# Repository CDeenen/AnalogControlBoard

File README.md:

# AnalogControlBoard
The analog control board (ACB) is a complete solution for all your analog and digital input and output needs. The board has 8 16-bit analog output ports, 16 16-bit analog input ports and 32 digital GPIOs (general purpose inputs/outputs). The board is controlled with a NXP LPC1768 microcontroller that can be communicated with through the USB port.

More info can be found in the wiki: https://github.com/CDeenen/AnalogControlBoard/wiki

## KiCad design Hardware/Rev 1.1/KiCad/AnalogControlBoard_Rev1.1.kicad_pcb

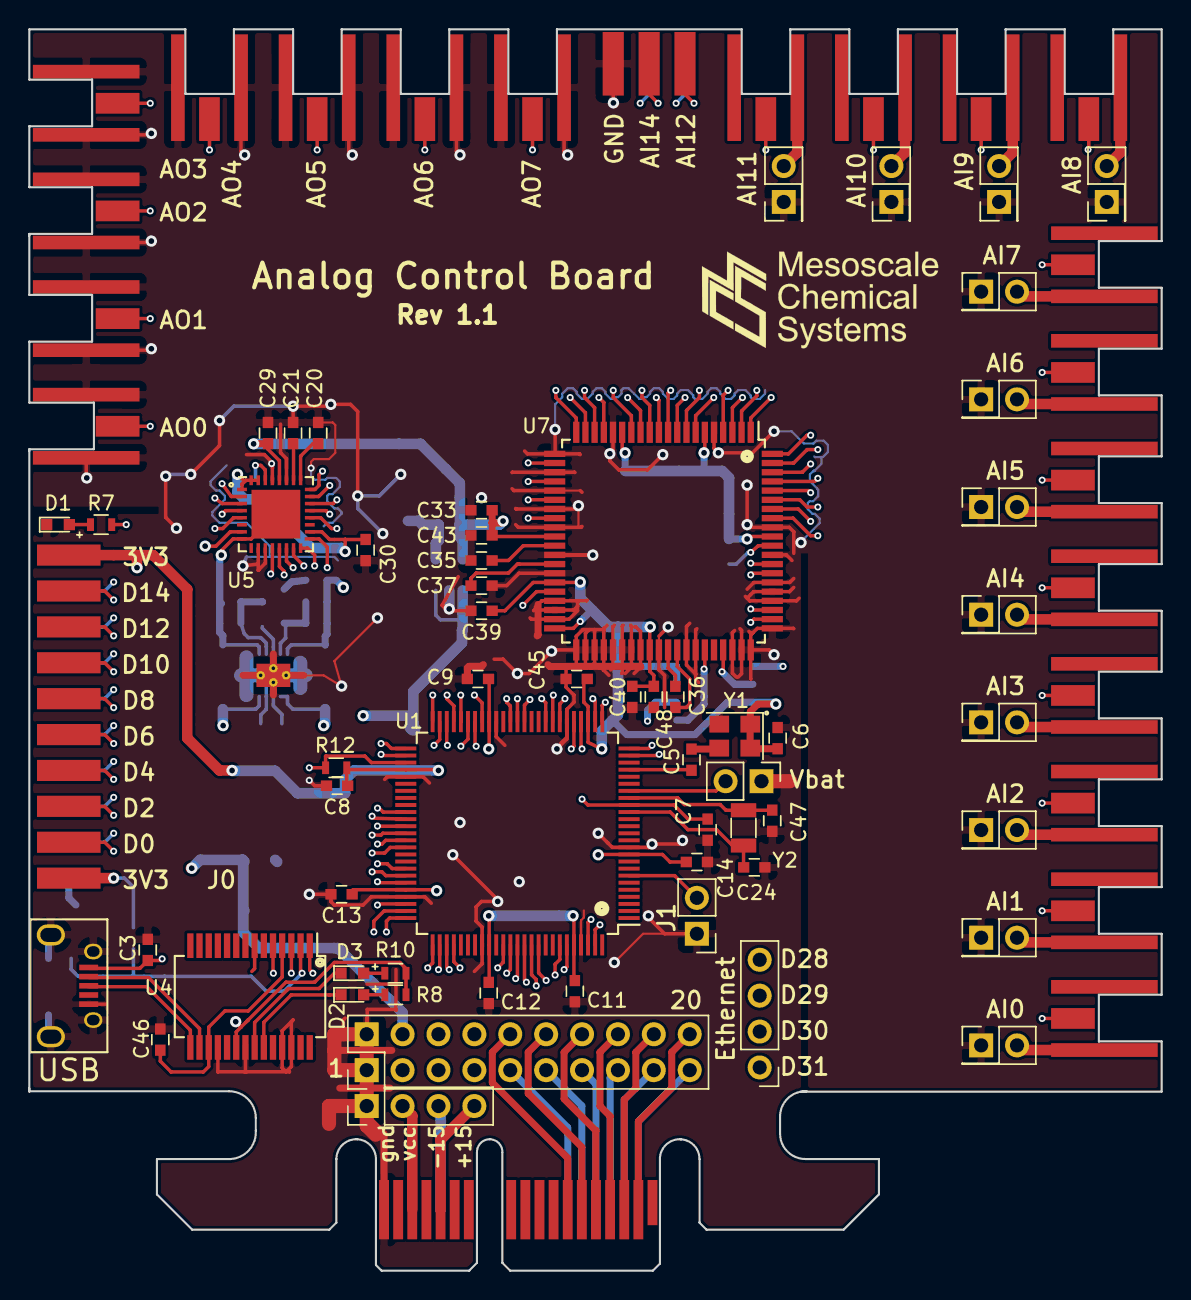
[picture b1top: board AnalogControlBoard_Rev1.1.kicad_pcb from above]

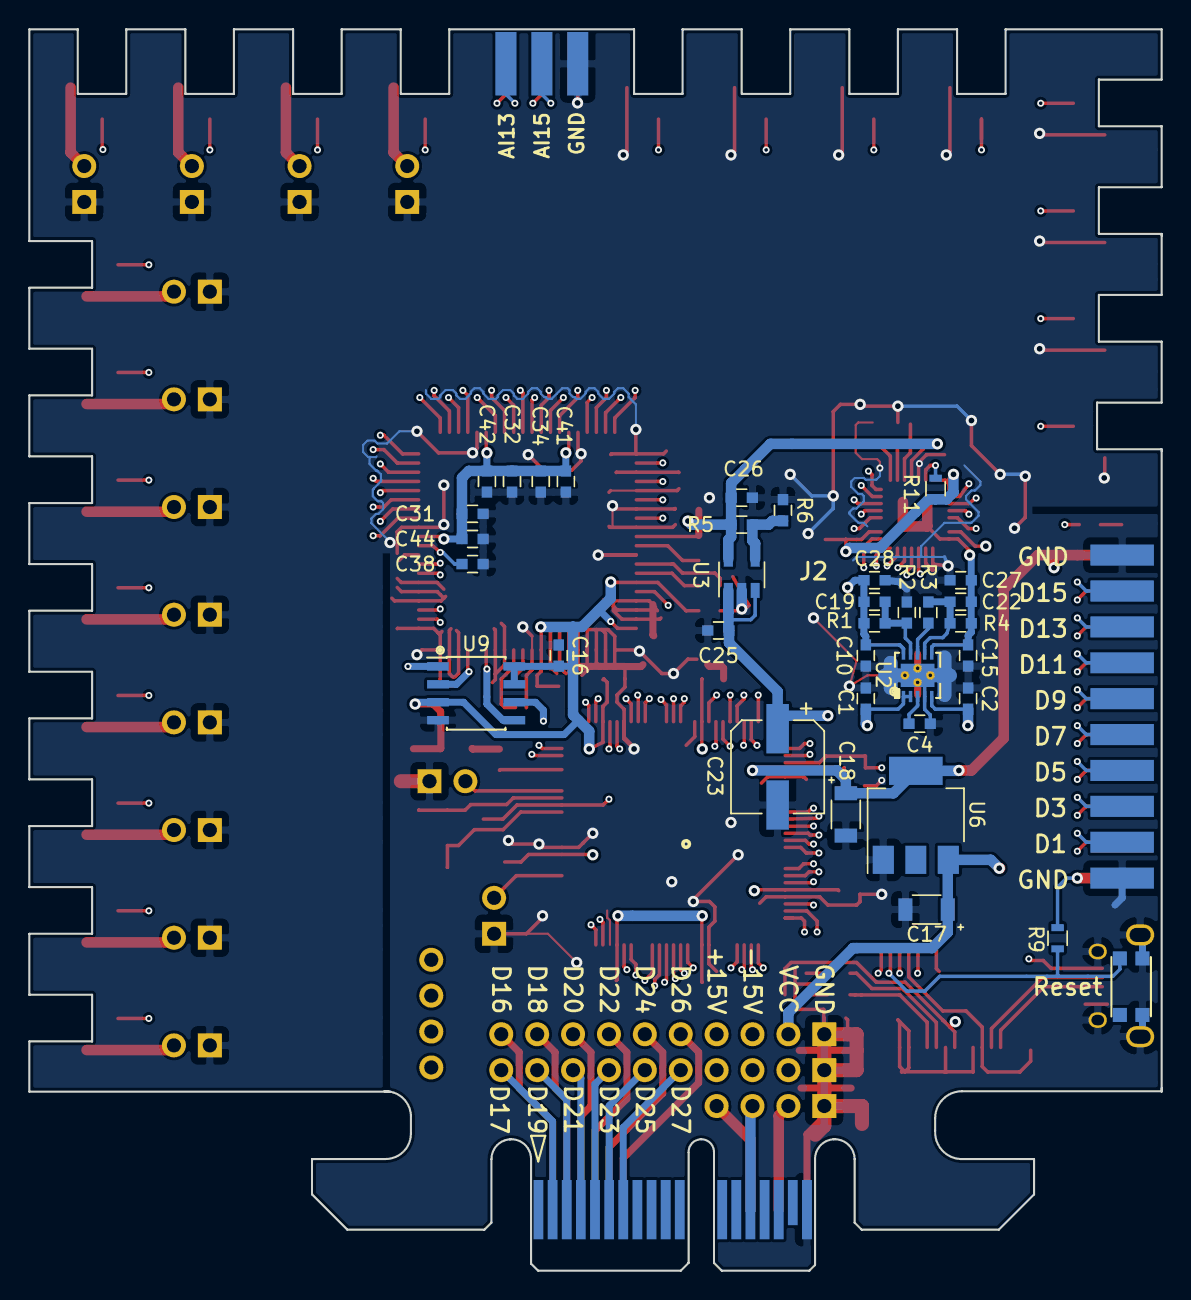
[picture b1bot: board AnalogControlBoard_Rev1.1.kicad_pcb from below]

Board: 4 copper layers, 80.1 x 87.9 mm, 115 parts (36 on the bottom side), 123 nets.

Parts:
C1, C2, C10, C15, C31, C32, C33, C34, C36, C38, C40: 10uF; C_0603
C3, C27, C28, C29, C39: 1uF; C_0603
C4, C19, C22: 10nF; C_0603
C5: 100pF; C_0603
C6, C7, C20, C21, C25, C26, C30, C41, C42, C43, C44, C46: 100nF; C_0603
C8, C9, C11, C12, C13, C14, C16, C45: 0.1uF; C_0603
C17: 10uF Tantalum; C_1206
C18: 22uF Tantalum; C_1206
C23: 100uF; CP_Elec_6.3x7.7
C24, C47: 18pF; C_0603
C35: 10uF Low ESR, X5R; C_0603
C37: 100nF, X8R; C_0603
C48: 100nF; Capacitor_0603
D1, D2, D3: LED; LED_0603
J1: EEPROM_CLEAR; Pin_Header_Straight_1x02_Pitch2.54mm
J2: Conn_02x10_Odd_Even; 2x10pinSideMount
J3: USB_OTG; MicroUSB_B
J4: Conn_PCI36; PCI-36
J5: JAI0; Pin_Header_Straight_2x01_Pitch2.54mm
J6: JAI1; Pin_Header_Straight_2x01_Pitch2.54mm
J7: JAI2; Pin_Header_Straight_2x01_Pitch2.54mm
J8: JAI3; Pin_Header_Straight_2x01_Pitch2.54mm
J9: JAI4; Pin_Header_Straight_2x01_Pitch2.54mm
J10: JAI5; Pin_Header_Straight_2x01_Pitch2.54mm
J11: JAI6; Pin_Header_Straight_2x01_Pitch2.54mm
J12: JAI7; Pin_Header_Straight_2x01_Pitch2.54mm
J13: JAI8; Pin_Header_Straight_2x01_Pitch2.54mm
J14: JAI9; Pin_Header_Straight_2x01_Pitch2.54mm
J15: JAI10; Pin_Header_Straight_2x01_Pitch2.54mm
J16: JAI11; Pin_Header_Straight_2x01_Pitch2.54mm
J17: Conn_02x03_Odd_Even; 2x3pinSideMount
J18, J20: Conn_01x04; Pin_Header_Straight_1x04_Pitch2.54mm
J22: Conn_02x10_Odd_Even; Pin_Header_Straight_2x10_Pitch2.54mm
J23: Vbat; Pin_Header_Straight_1x02_Pitch2.54mm
P1: AI0; MMCXconnector
P3: AI1; MMCXconnector
P6: AI2; MMCXconnector
P7: AI3; MMCXconnector
P8: AI4; MMCXconnector
P9: AI5; MMCXconnector
P10: AI6; MMCXconnector
P11: AI7; MMCXconnector
P12: AI8; MMCXconnector
P13: AI9; MMCXconnector
P14: AI10; MMCXconnector
P15: AI11; MMCXconnector
P20: AO3; MMCXconnector
P21: AO2; MMCXconnector
P22: AO1; MMCXconnector
P23: AO0; MMCXconnector
P24: AO7; MMCXconnector
P25: AO6; MMCXconnector
P26: AO5; MMCXconnector
P27: AO4; MMCXconnector
R1: 90.9K; C_0603
R2, R3: 10K; C_0603
R4: 100K; C_0603
R5: 76.8K; C_0603
R6: 24.9K; C_0603
R7, R8, R10: 220R; R_0603
R9, R11, R12: 10K; R_0603
SW1: SW_DPST; Switch
U1: LPC1768; LQFP-100_14x14mm_Pitch0.5mm
U2: TPS7A39; WSON-10_3x3mm_Pitch0.5mm_ThermalVias
U3: TPS73201-EP; SOT-23-5
U4: FT232RL; SSOP-28_5.3x10.2mm_Pitch0.65mm
U5: LTC2666; QFN-32-1EP_5x5mm_Pitch0.5mm
U6: LM1117; SOT-223-3_TabPin2
U7: AD7616; LQFP-80_14x14mm_Pitch0.65mm
U9: AT25_EEPROM; SOIC-8_3.9x4.9mm_Pitch1.27mm
Y1: ASE_12_LCT; Crystal_SMD_3225-4pin_3.2x2.5mm
Y2: 32.768KHz RTC Crystal; Crystal_SMD_3215-2pin_3.2x1.5mm

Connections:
3v3: C6.2, C8.1, C9.1, C11.1, C12.1, C13.1, C14.1, C16.2, C18.1, C30.1, C39.1, C40.1, C45.1, C48.1, J2.1, J2.19, R9.2, R11.2, R12.1, U1.10, U1.28, U1.42, U1.54, U1.71, U1.84, U1.96, U5.1, U5.18, U5.31, U5.32, U6.2, U7.35, U7.40, U7.49, U9.3, U9.7, U9.8, Y1.1, Y1.4
5V: C26.2, C29.2, C31.2, C32.2, C33.2, C34.2, C41.2, C42.2, C43.2, C44.2, R5.2, U3.5, U5.28, U7.6, U7.15, U7.30, U7.71
+7Vanalog: J4.A17, J4.B17
+7Vdigital: C17.1, C23.1, C25.2, J4.A16, J4.B16, J20.2, J22.3, J22.4, U3.1, U3.3, U6.3
+12V: C10.1, C19.1, C28.2, R1.2, U2.10, U5.7
+15V: C1.1, J4.A14, J20.4, J22.7, J22.8, U2.1, U2.2
-12V: C15.2, C22.2, C27.2, R4.1, U2.6, U5.8
-15V: C2.2, J4.B14, J20.3, J22.5, J22.6, U2.5
AB12: J4.A12, J4.B12
AD_BUSY: U1.32, U7.67
AD_CONVST: U1.33, U7.68
AD_CS: U1.27, U7.63
AD_MISO: U1.37, U5.15, U7.57, U9.2
AD_MOSI: U1.38, U5.16, U7.55, U9.5
AD_RESET: U1.39, U7.36
AD_SCLK: U1.34, U5.14, U7.62, U9.6
AI0: P1.2, U7.73
AI0_GND: J5.2, P1.1, U7.74
AI1: P3.2, U7.75
AI1_GND: J6.2, P3.1, U7.76
AI2: P6.2, U7.77
AI2_GND: J7.2, P6.1, U7.78
AI3: P7.2, U7.79
AI3_GND: J8.2, P7.1, U7.80
AI4: P8.2, U7.2
AI4_GND: J9.2, P8.1, U7.1
AI5: P9.2, U7.4
AI5_GND: J10.2, P9.1, U7.3
AI6: P10.2, U7.7
AI6_GND: J11.2, P10.1, U7.8
AI7: P11.2, U7.9
AI7_GND: J12.2, P11.1, U7.10
AI8_GND: J13.2, P12.1, U7.11
AI9: P13.2, U7.14
AI9_GND: J14.2, P13.1, U7.13
AI10: P14.2, U7.17
AI10_GND: J15.2, P14.1, U7.18
AI11: P15.2, U7.19
AI11_GND: J16.2, P15.1, U7.20
AI12: J17.5, U7.22
AI13: J17.6, U7.24
AI14: J17.3, U7.26
AI15: J17.4, U7.28
EEPROM_CS: U1.26, U9.1
EnetRxD0: J18.2, U1.91
EnetRxD1: J18.1, U1.90
EnetTxD0: J18.4, U1.95
EnetTxD1: J18.3, U1.94
GND: C1.2, C2.1, C3.2, C4.1, C6.1, C7.2, C8.2, C9.2, C10.2, C11.2, C12.2, C13.2, C14.2, C15.1, C16.1, C17.2, C18.2, C20.1, C21.2, C23.2, C24.2, C25.1, C26.1, C27.1, C28.1, C29.1, C30.2, C31.1, C32.1, C33.1, C34.1, C35.1, C37.2, C38.1, C39.2, C40.2, C41.1, C42.1, C43.1, C44.1, C45.2, C46.1, C47.2, C48.2, D1.1, J1.1, J2.2, J2.20, J3.5, J3.6, J4.A18, J4.B18, J5.1, J6.1, J7.1, J8.1, J9.1, J10.1, J11.1, J12.1, J13.1, J14.1, J15.1, J16.1, J17.1, J17.2, J20.1, J22.1, J22.2, J23.1, P20.1, P21.1, P22.1, P23.1, P24.1, P25.1, P26.1, P27.1, R2.1, R6.2, SW1.2, U1.11, U1.31, U1.41, U1.55, U1.72, U1.83, U1.97, U2.4, U3.2, U4.21, U4.25, U4.26, U5.10, U5.11, U5.27, U5.29, U6.1, U7.5, U7.16, U7.21, U7.23, U7.25, U7.27, U7.29, U7.32, U7.34, U7.37, U7.38, U7.39, U7.41, U7.42, U7.43, U7.44, U7.45, U7.46, U7.47, U7.48, U7.50, U7.53, U7.54, U7.58, U7.59, U7.60, U7.61, U7.64, U7.65, U7.66, U7.69, U7.72, U9.4, Y1.2
GPIO_CS: J2.11, U1.63
GPIO_INT0: J2.16, U1.51
GPIO_INT1: J2.15, U1.52
GPIO_MISO: J2.13, U1.61
GPIO_MOSI: J2.14, U1.60
GPIO_PWM0: J2.8, U1.68
GPIO_PWM1: J2.7, U1.69
GPIO_PWM2: J2.6, U1.70
GPIO_PWM3: J2.5, U1.73
GPIO_RX: J2.10, U1.64
GPIO_SCK: J2.12, U1.62
GPIO_SCL: J2.18, U1.47
GPIO_SDA: J2.17, U1.46
GPIO_TX: J2.9, U1.65
GPIO_USB_D+: J2.3, U1.29
GPIO_USB_D-: J2.4, U1.30
ISP_SEL: R12.2, U1.53, U4.3
LTC_CLR: U1.48, U5.24
LTC_CS: U1.44, U5.13
LTC_LDAC: U1.45, U5.12
LTC_OVRTMP: R11.1, U1.49, U5.30
LTC_TGP: U1.43, U5.17
unnamed: C4.2, U2.3
unnamed: C5.1, U1.22
unnamed: C5.2, Y1.3
unnamed: C19.2, R1.1, R2.2, U2.9
unnamed: C20.2, U5.25
unnamed: C21.1, U5.26
unnamed: C22.1, R3.1, R4.2, U2.7
unnamed: C24.1, U1.16, Y2.1
unnamed: C35.2, U7.31
unnamed: C36.1, U7.51
unnamed: C36.2, U7.52
unnamed: C37.1, U7.33
unnamed: C38.2, U7.70
unnamed: C46.2, U4.4, U4.17
unnamed: C47.1, U1.18, Y2.2
unnamed: D1.2, R7.1
unnamed: D2.1, U4.23
unnamed: D2.2, R8.1
unnamed: D3.1, U4.22
unnamed: D3.2, R10.1
unnamed: J1.2, U1.7
unnamed: J3.2, U4.16
unnamed: J3.3, U4.15
unnamed: J23.2, U1.19
unnamed: P20.2, U5.2
unnamed: P21.2, U5.3
unnamed: P22.2, U5.4
unnamed: P23.2, U5.5
unnamed: P24.2, U5.20
unnamed: P25.2, U5.21
unnamed: P26.2, U5.22
unnamed: P27.2, U5.23
unnamed: R3.2, U2.8
unnamed: R5.1, R6.1, U3.4
unnamed: R7.2, U1.50
PCI_GPIO0: J4.B5, J22.13, U1.89
PCI_GPIO1: J4.A5, J22.14, U1.88
PCI_GPIO2: J4.B6, J22.11, U1.87
PCI_GPIO3: J4.A6, J22.12, U1.86
PCI_I2C_SCL: J4.A2, J22.20, U1.24
PCI_I2C_SDA: J4.B2, J22.19, U1.25
PCI_SPI_MISO: J4.A4, J22.16, U1.77
PCI_SPI_MOSI: J4.B4, J22.15, U1.76
PCI_SPI_SCK: J4.B3, J22.17, U1.78
PCI_SPI_SSEL: J4.A3, J22.18, U1.79
PCI_UART_RX: J4.B7, J22.9, U1.74
PCI_UART_TX: J4.A7, J22.10, U1.75
RESET: C7.1, R9.1, SW1.1, U1.17, U4.2
USB_RX: U1.99, U4.1
USB_TX: U1.98, U4.5
V1: J4.A13, J4.B13
Vbus: C3.1, J3.1, R8.2, R10.2, U4.20

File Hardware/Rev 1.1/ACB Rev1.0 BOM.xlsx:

Column2 | Reference(s) | Value | Footprint | Specific | Article Nr
11 | C1, C2, C10, C15, C31, C32, C33, C34, C36, C38, C40 | 10uF | SMD 0603
5 | C3, C27, C28, C29, C39 | 1uF | SMD 0603
3 | C4, C19, C22 | 10nF | SMD 0603
1 | C5 | 100pF | SMD 0603
21 | C6, C7, C8, C9, C11, C12, C13, C14, C16, C20, C21, C25, C26, C30, C41, C42, C43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 | 100nF | SMD 0603
1 | C17 | 10uF Tantalum | SMD 1206
1 | C18 | 22uF Tantalum | SMD 1206
1 | C23 | 100uF | SMD 6.3x7.7
2 | C24, C47 | 18pF | SMD 0603
1 | C35 | 10uF Low ESR, X5R | SMD 0603
1 | C37 | 100nF, X8R | SMD 0603
1 | R1 | 90.9K | SMD 0603
5 | R2, R3, R9, R11, R12 | 10K | SMD 0603
1 | R4 | 100K | SMD 0603
1 | R5 | 76.8K | SMD 0603
1 | R6 | 24.9K | SMD 0603
3 | R7, R8, R10 | 220R | SMD 0603
3 | D1, D2, D3 | LED | SMD 0603
14 | J1, J5, J6, J7, J8, J9, J10, J11, J12, J13, J14, J15, J16, J23 | 1x2 Pin Header | 1x2 Pin Header
2 | J2, J22 | 2x10 Pin Header | 2x10 Pin Header
1 | J17 | 2x3 Pin Header | 2x3 Pin Header
2 | J18, J20 | 1x4 Pin Header | 1x4 Pin Header
1 | J3 | USB_OTG | MicroUSB_B | HRS | ZX62D-B-5P8(30)
20 | P1, P3, P6, P7, P8, P9, P10, P11, P12, P13, P14, P15, P20, P21, P22, P23, P24, 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 | MMCX Connector | MMCXconnector - Edge Mount | Molex | 73415-0961
1 | SW1 | Switch | Switch | C&K | KMR231GLFS
1 | U1 | LPC1768 | LQFP-100_14x14mm_Pitch0.5mm | NPX | LPC1768FBD100
1 | U2 | TPS7A39 | WSON-10_3x3mm_Pitch0.5mm_ThermalVias | Texas Instruments | TPS7A3901DSCT
1 | U3 | TPS73201-EP | SOT-23-5 | Texas Instruments | TPS73201MDBVREP
1 | U4 | FT232RL | SSOP-28_5.3x10.2mm_Pitch0.65mm | FTDI | FT232RL
1 | U5 | LTC2666 | QFN-32-1EP_5x5mm_Pitch0.5mm | Analog Devices | LTC2666HUH-16
1 | U6 | LM1117-3.3 | SOT-223-3_TabPin2 | Texas Instruments | LM1117IMPX-3.3/NOPB
1 | U7 | AD7616 | LQFP-80_14x14mm_Pitch0.65mm | Analog Devices | AD7616BSTZ
1 | U9 | AT25_EEPROM | SOIC-8_3.9x4.9mm_Pitch1.27mm | Microchip | AT25320B-SSHL-B
1 | Y1 | 12MHz Crystal | SMD_3225-4pin_3.2x2.5mm | Abracon | ASE-12.000MHZ-LC-T
1 | Y2 | 32.768KHz RTC Crystal | SMD_3215-2pin_3.2x1.5mm | Epson | Q13FC13500005 FC-135 32.768KHZ 12.5PF
1 | External PSU |  |  | Cosel | LDC30F-2-SNY
12 | Jumpers

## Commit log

2020-07-23 Create asdf
